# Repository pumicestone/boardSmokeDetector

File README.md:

# boardSmokeDetector
Board for the smoke detector (holder)

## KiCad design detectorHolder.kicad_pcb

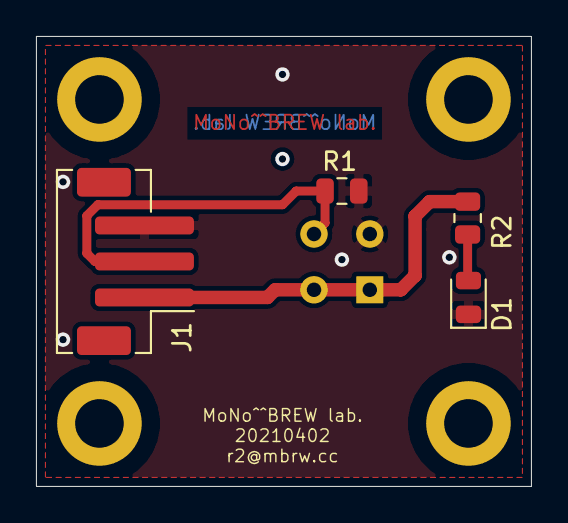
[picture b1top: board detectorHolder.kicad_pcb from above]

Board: 2 copper layers, 27.5 x 25.0 mm, 9 parts (1 on the bottom side), 4 nets.

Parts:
D1: LED RED; LED_0805_2012Metric
H1, H2, H3, H4: MountingHole; MountingHole_2.7mm_M2.5_DIN965_Pad
J1: Conn_01x03; JST_PH_B3B-PH-SM4-TB_1x03-1MP_P2.00mm_Vertical
J2: MP801
R1: R; R_0805_2012Metric
R2: 330R; R_0805_2012Metric

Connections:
+5V: J1.1, J2.1, J2.3, R2.2
/SIGNAL: J1.2, J2.4, R1.2
GND: D1.1, J1.3, J2.2, R1.1
unnamed: D1.2, R2.1

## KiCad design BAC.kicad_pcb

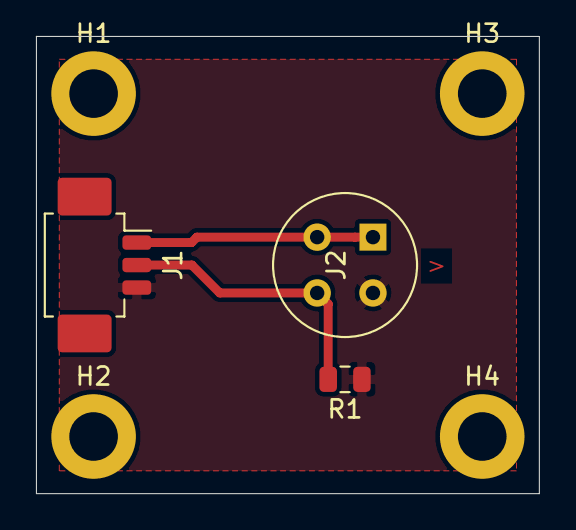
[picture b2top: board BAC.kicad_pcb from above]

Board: 2 copper layers, 27.9 x 25.4 mm, 7 parts (0 on the bottom side), 3 nets.

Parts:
H1, H2, H3, H4: MountingHole; MountingHole_2.7mm_M2.5_DIN965_Pad
J1: Conn_01x03; Molex_PicoBlade_53261-0371_1x03-1MP_P1.25mm_Horizontal
J2: Conn_02x02_Odd_Even; MP801
R1: R; R_0805_2012Metric

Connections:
+5V: J1.1, J2.1, J2.3
/SIGNAL: J1.2, J2.4, R1.2
GND: J1.3, J2.2, R1.1

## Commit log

2019-10-17 First schematic of the holder
2021-01-10 PCBWAY production files (20210110)
2021-04-02 Sensor filpped. Production files (PCBWAY)
